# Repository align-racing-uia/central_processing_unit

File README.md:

<h1 align="center"> Central Processing Unit </h1> <br>
<p align="center">
    
</p>

<!-- START doctoc generate TOC please keep comment here to allow auto update -->
<!-- DON'T EDIT THIS SECTION, INSTEAD RE-RUN doctoc TO UPDATE -->
## Table of contents

- [Introduction](#introduction)
- [Align Racing UiA](#alignracinguia)
- [Rules for file structure](#rulesforfilestructure)
- [License](#license)

<!-- END doctoc generated TOC please keep comment here to allow auto update -->

## Introduction

This is the repository for Align Racing's formula student race car's different systems.

## Align Racing UiA

<a href="http://www.alignracing.no/">Align Racing UiA (AR)</a> is a multidisciplinary student organisation at <a href="https://www.uia.no/">The University of Agder (UiA)</a>, that take part in the world’s largest yearly engineering competition; <a href="https://www.imeche.org/events/formula-student">Formula Student (FS)</a>. The organisation continuously consists of around 60 students, from a wide variety of disciplines. The competition includes developing, building, budgeting and marketing a small scale formula type racing car. AR takes this a bit further by having more focus on developing a strong organisation, open for all disciplines, that gives the members a taste of future work-life.

## Rules

## Contribution

## License
All content included in this Git repository is under the license:

Creative Commons Attribution-NonCommercial-ShareAlike 4.0 International

You are free to:
* <b> Share </b> — copy and redistribute the material in any medium or format
* <b> Adapt </b> — remix, transform, and build upon the material

Under the following terms:
* <b> Attribution </b> — You must give appropriate credit, provide a link to the license, and indicate if changes were made. You may do so in any reasonable manner, but not in any way that suggests the licensor endorses you or your use.
* <b> NonCommercial </b> — You may not use the material for commercial purposes.
* <b> ShareAlike </b> — If you remix, transform, or build upon the material, you must distribute your contributions under the same license as the original.
* <b> No additional restrictions </b> — You may not apply legal terms or technological measures that legally restrict others from doing anything the license permits.

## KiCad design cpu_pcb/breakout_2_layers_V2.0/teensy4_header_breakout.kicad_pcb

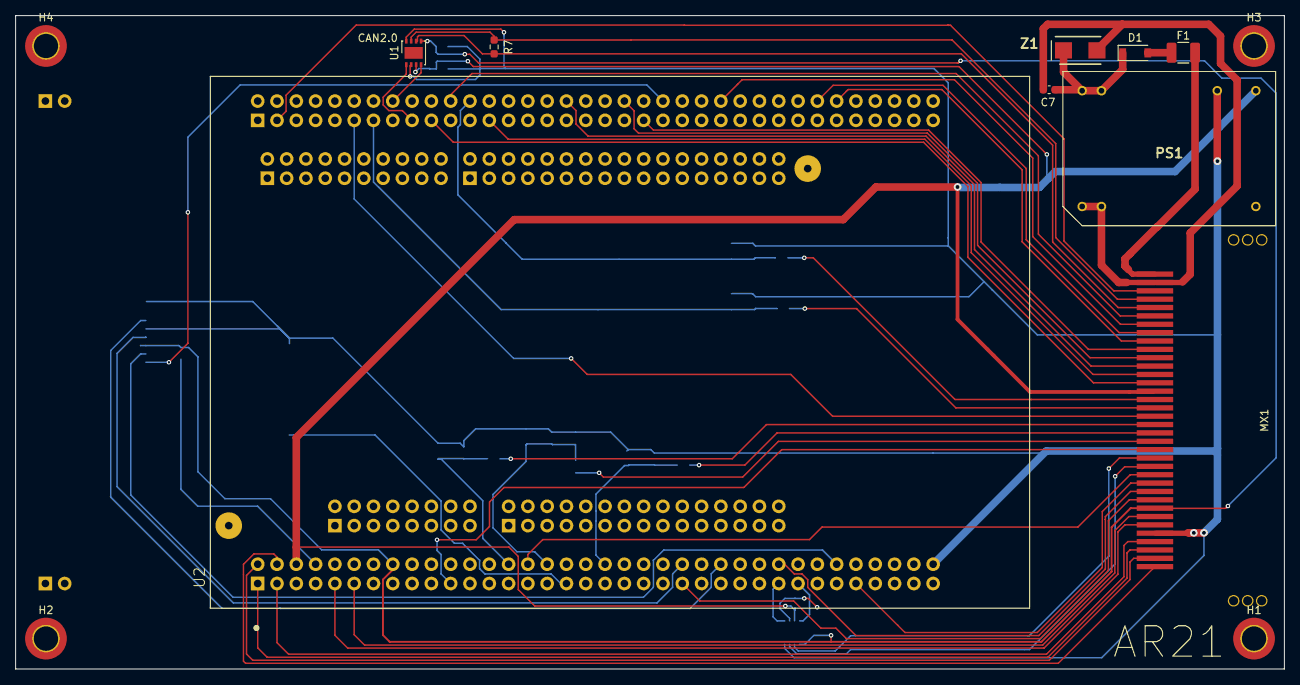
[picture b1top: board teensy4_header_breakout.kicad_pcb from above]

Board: 2 copper layers, 167.0 x 86.0 mm, 38 parts (0 on the bottom side), 52 nets.

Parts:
C1, C2, C3, C4, C5: 15n; C_0603_1608Metric
C6, C7, C8, C9, C10, C11: 10uF; C_0603_1608Metric
D1: D_Schottky_MBR0520LT1G; D_SOD-123-MBR0520LT1G
D2, D3, D4, D5, D6: D_Zener_MM3Z3V6T1G; D_SOD-323-MM3Z3V6T1G
F1: Polyfuse_Small; R_1210_3225Metric_Pad1.30x2.65mm_HandSolder
H1, H2, H3, H4: MountingHole; MountingHole_3.2mm_M3_ISO14580_Pad_TopBottom
MX1: MX34_36_pins; Connector_MX34_36pins
PS1: TEL_5-1211; TEL51211
R1, R2, R3, R4, R5: 10k; R_0603_1608Metric
R6: 20k; R_0603_1608Metric
R7, R8: 120; R_0603_1608Metric_Pad0.98x0.95mm_HandSolder
SDcard1: Micro_SD_Card; Molex_502774-0891
U1, U3: MCP2542WFDxMF; DFN-8-1EP_3x3mm_P0.65mm_EP1.55x2.4mm
U2: NUCLEO-H745ZI-Q; MODULE_NUCLEO-F429ZI
U4: S8211-46R
Z1: 1SMB5930BT3G; DIOM5436X247N

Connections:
4G-RX: MX1.1, U2.CN11_4
4G-TX: MX1.4, U2.CN11_3
12V_GND: C7.1, MX1.35, PS1.2, PS1.3, Z1.2
12V_IN: F1.1, MX1.36
12V_safe: C7.2, D1.1, PS1.22, PS1.23, Z1.1
+3V3: C6.2, C8.2, C10.2, MX1.8, SDcard1.4, U1.5, U2.CN11_16, U3.5
+5V: C9.1, C11.1, MX1.22, PS1.14, U1.3, U2.CN11_6, U3.3
CAN2.0-CANH: MX1.33, R7.1, U1.7
CAN2.0-CANL: MX1.32, R7.2, U1.6
CAN2.0-RX: U1.4, U2.CN12_16
CAN2.0-TX: U1.1, U2.CN12_17
CANFD-CANH: MX1.13, R8.1, U3.7
CANFD-CANL: MX1.14, R8.2, U3.6
CANFD-RX: U2.CN11_57, U3.4
CANFD-TX: U2.CN11_55, U3.1
ClutchPS: MX1.16, R5.1
ClutchPSFiltered: C5.1, D2.1, R5.2, R6.1, U2.CN11_32
GND: C1.2, C2.2, C3.2, C4.2, C5.2, C6.1, C8.1, C9.2, C10.1, C11.2, D2.2, D3.2, D4.2, D5.2, D6.2, MX1.5, PS1.16, R6.2, SDcard1.6, SDcard1.9, U1.2, U1.8, U1.9, U2.CN11_8, U2.CN11_72, U2.CN12_72, U3.2, U3.8, U3.9, U4.3
GPIO-analog-ut1: MX1.30, U2.CN12_50
GPIO-analog-ut2: MX1.29, U2.CN12_60
GPIO-digital1: MX1.31, U2.CN12_22
GPIO-digital2: MX1.28, U2.CN12_62
GearPS-CS: MX1.26, U2.CN12_40
GearPS-MISO: MX1.11, U2.CN11_63
GearPS-MOSI: MX1.9, U2.CN11_45
GearPS-SCK: MX1.19, U2.CN12_11
I2C1-SCL: MX1.34, U2.CN12_3
I2C1-SDA: MX1.15, U2.CN11_21
unnamed: D1.2, F1.2
unnamed: U2.CN11_33, U4.1
SD-CS: SDcard1.2, U2.CN12_44
SD-MISO: SDcard1.7, U2.CN11_50
SD-MOSI: SDcard1.3, U2.CN11_62
SD-SCK: SDcard1.5, U2.CN11_46
Servo-IO: MX1.10, U2.CN11_56
Servo-RX: MX1.6, U2.CN11_9
Servo-TX: MX1.7, U2.CN11_11
StearingAS: MX1.25, U2.CN12_34
SusDips-FL: MX1.20, R2.2
SusDips-FR: MX1.18, R1.2
SusDips-RL: MX1.17, R4.2
SusDips-RR: MX1.21, R3.2
SusDipsFiltered-FL: C2.1, D5.1, R2.1, U2.CN12_13
SusDipsFiltered-FR: C1.1, D3.1, R1.1, U2.CN11_28
SusDipsFiltered-RL: C4.1, D6.1, R4.1, U2.CN11_38
SusDipsFiltered-RR: C3.1, D4.1, R3.1, U2.CN12_24
VN-RX: MX1.2, U2.CN11_2
VN-TX: MX1.3, U2.CN11_1
WSHE-FL: MX1.23, U2.CN12_19
WSHE-FR: MX1.24, U2.CN12_25
WSHE-RL: MX1.12, U2.CN11_30
WSHE-RR: MX1.27, U2.CN12_41

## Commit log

2021-08-01 Cleanup and renaming.
2021-08-01 Directory delete before merge.
2021-08-01 Moved folders.
